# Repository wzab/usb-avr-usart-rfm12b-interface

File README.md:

usb-avr-usart-rfm12b-interface
=============================

Small interface board allowing you to control yor microcontroller wirelessly via RFM12B module (USART also available)

Please note, that even though my part of this design is published under permissive MIT license,
it uses some software libraries, which are published under other (e.g. GPL) license.
Please check license of every component before you reuse this design (especially for commercial puposes).

The PCB design is done so, that it may be manufactured as single-sided PCB with minimal number of jumpers.

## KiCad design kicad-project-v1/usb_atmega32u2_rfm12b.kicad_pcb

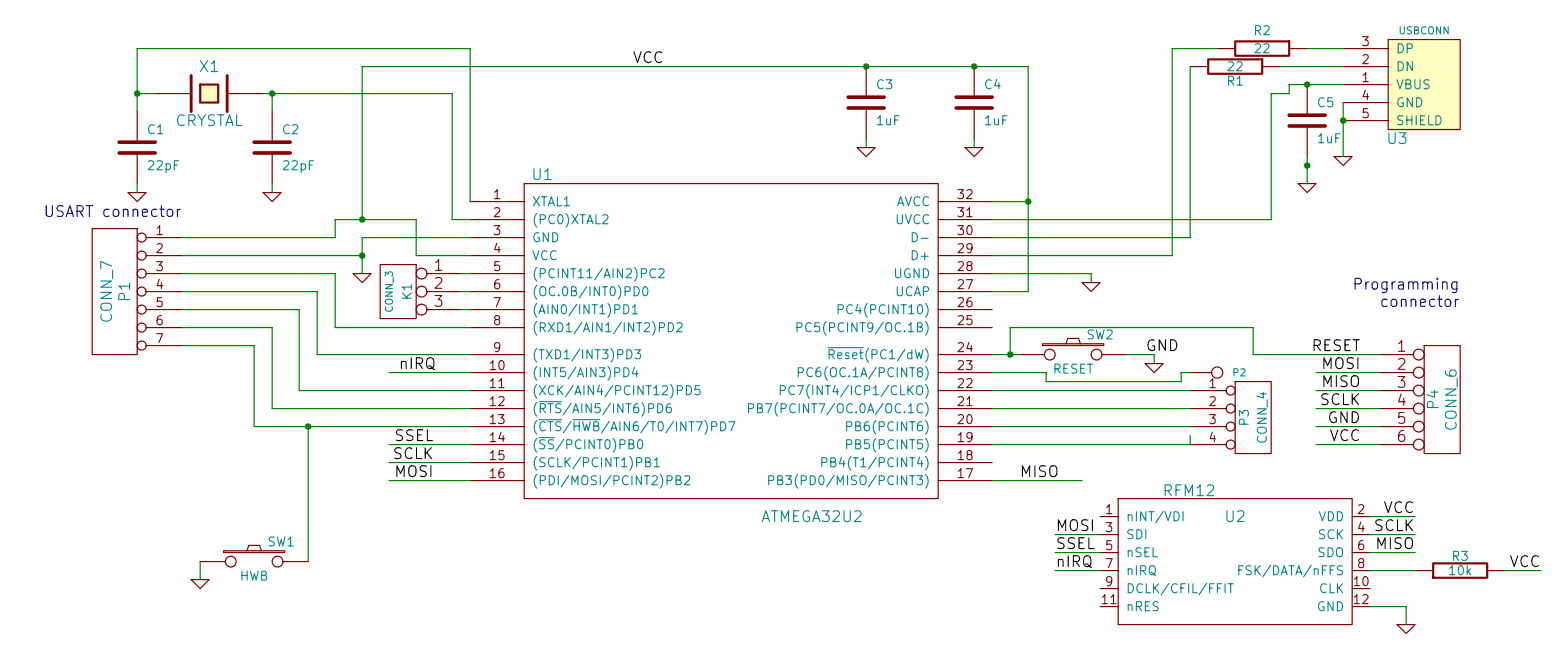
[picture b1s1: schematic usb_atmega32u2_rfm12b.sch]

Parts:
C1, C2: 22pF
C3, C4, C5: 1uF
K1: CONN_3
P1: CONN_7
P2: CONN_1
P3: CONN_4
P4: CONN_6
R1, R2: 22
R3: 10k
SW1: HWB
SW2: RESET
U1: ATMEGA32U2; TQFP32
U2: RFM12
U3: USBCONN
X1: CRYSTAL

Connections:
/MISO: P4.3, U1.17 (PB3(PD0/MISO/PCINT3)), U2.6 (SDO)
/MOSI: P4.2, U1.16 ((PDI/MOSI/PCINT2)PB2), U2.3 (SDI)
/RESET: P4.1, SW2.1, U1.24 (~Reset~(PC1/dW)); also elsewhere on the board
/SCLK: P4.4, U1.15 ((SCLK/PCINT1)PB1), U2.4 (SCK)
/SSEL: U1.14 ((~SS~/PCINT0)PB0), U2.5 (nSEL)
/VCC: C3.1, C4.1, P1.1, P4.6, R3.2, U1.4 (VCC), U1.27 (UCAP), U1.32 (AVCC), U2.2 (VDD); also elsewhere on the board
/nIRQ: U1.10 ((INT5/AIN3)PD4), U2.7 (nIRQ)
GND: C1.2, C2.2, C3.2, C4.2, C5.2, P1.2, P4.5, SW1.1, SW2.2, U1.3 (GND), U1.28 (UGND), U2.12 (GND), U3.4 (GND), U3.5 (SHIELD)
unnamed: P1.3, U1.8 ((RXD1/AIN1/INT2)PD2)
unnamed: P1.4, U1.9 ((TXD1/INT3)PD3)
unnamed: P1.5, U1.11 ((XCK/AIN4/PCINT12)PD5)
unnamed: P1.6, U1.12 ((~RTS~/AIN5/INT6)PD6)
unnamed: R3.1, U2.8 (FSK/DATA/nFFS)
unnamed: P3.2, U1.21 (PB7(PCINT7/OC.0A/OC.1C))
unnamed: P3.1, U1.22 (PC7(INT4/ICP1/CLKO))
unnamed: P2.1, U1.23 (PC6(OC.1A/PCINT8))
unnamed: P3.4, U1.19 (PB5(PCINT5))
unnamed: R2.2, U1.29 (D+)
unnamed: C5.1, U1.31 (UVCC), U3.1 (VBUS)
unnamed: R1.1, U3.2 (DN)
unnamed: R1.2, U1.30 (D-)
unnamed: R2.1, U3.3 (DP)
unnamed: C1.1, U1.1 (XTAL1), X1.1
unnamed: K1.1, U1.5 ((PCINT11/AIN2)PC2)
unnamed: K1.2 (PM), U1.6 ((OC.0B/INT0)PD0)
unnamed: K1.3, U1.7 ((AIN0/INT1)PD1)
unnamed: P3.3, U1.20 (PB6(PCINT6))
unnamed 27: P1.7, SW1.2, U1.13 ((~CTS~/~HWB~/AIN6/T0/INT7)PD7); also elsewhere on the board
unnamed: C2.1, U1.2 ((PC0)XTAL2), X1.2

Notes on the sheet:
USART connector
Programming connector

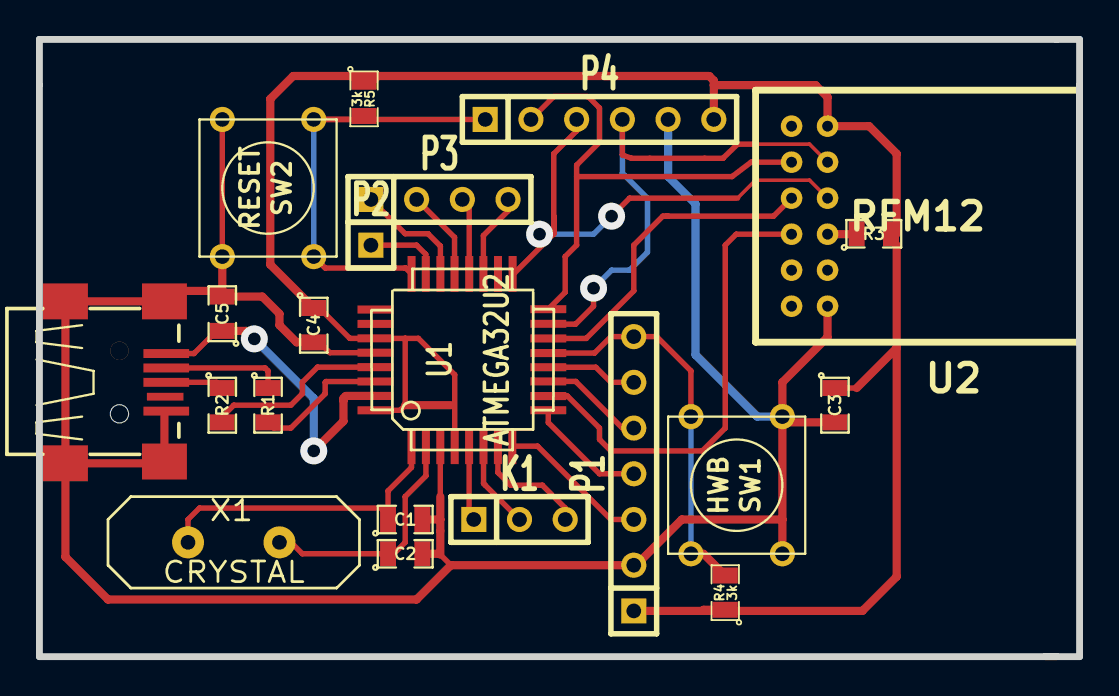
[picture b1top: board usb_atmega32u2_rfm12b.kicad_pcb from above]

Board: 2 copper layers, 57.8 x 34.3 mm, 21 parts (0 on the bottom side), 29 nets.

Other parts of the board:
R4, R5: 3k; SM0805

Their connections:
/RESET: R5.2; also elsewhere on the board
/VCC: R4.1, R5.1; also elsewhere on the board
unnamed 27: R4.2; also elsewhere on the board

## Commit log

2013-10-16 Added first version of PCB
2013-10-16 small correction
2013-11-03 Translated to the new version of Kicad (07.2013)
2013-12-06 Added pull-up resistors on HWB and RESET.
